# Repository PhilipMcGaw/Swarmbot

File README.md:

# SwarmBot

## Physical design constraints

* Smallest 3D Printer maximum dimensions 100 x 100 x 100
* Largest Cheap PCB from China 100 x 100 FR4 (50¢ each)

## People who have contributed

 * Philip 'Skippy' McGaw - philip@mcgaw.eu - https://philipmcgaw.com
 * Tamarisk 'NotQuiteHere' McGaw - tamarisk@mcgaw.eu - https://tamarisk.it
 * Bob 'thinkl33t' Clough - bob@clough.me - https://thinkl33t.co.uk

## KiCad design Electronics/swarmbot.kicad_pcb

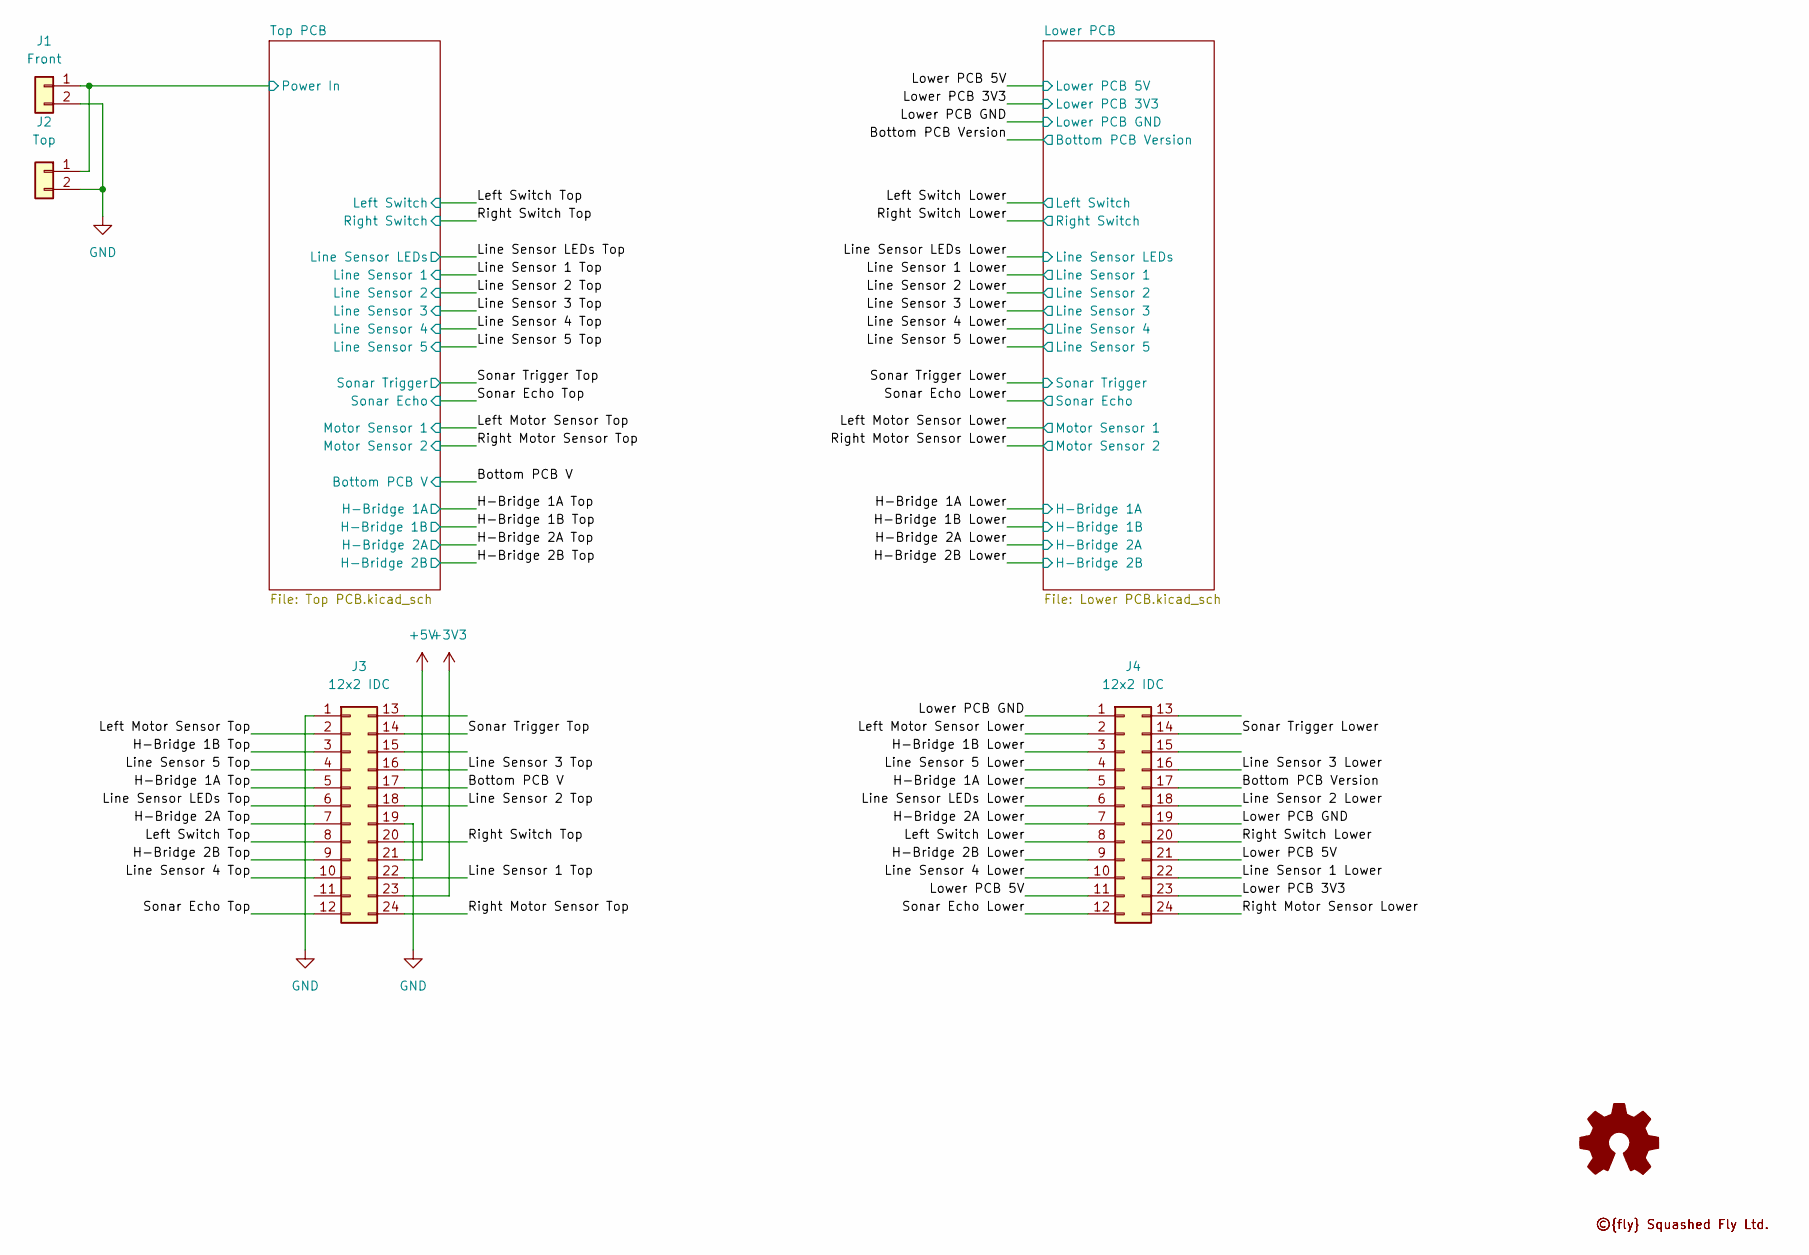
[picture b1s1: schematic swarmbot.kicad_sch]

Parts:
J1: Front; JST_XH_B2B-XH-A_1x02_P2.50mm_Vertical
J2: Top; JST_XH_B2B-XH-A_1x02_P2.50mm_Vertical
J3, J4: 12x2 IDC; IDC-Header_2x12_P2.54mm_Vertical
LOGO1: Logo_Open_Hardware_Small; OSHW-Logo2_7.3x6mm_SilkScreen
Logo1, Logo2: SquashedFlyLogo; SquashedFlySilk

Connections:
+3V3: J3.23; also elsewhere on the board
+5V: J3.21; also elsewhere on the board
/Bottom PCB V: J3.17; also elsewhere on the board
/Bottom PCB Version: J4.17; also elsewhere on the board
/H-Bridge 1A Lower: J4.5; also elsewhere on the board
/H-Bridge 1A Top: J3.5; also elsewhere on the board
/H-Bridge 1B Lower: J4.3; also elsewhere on the board
/H-Bridge 1B Top: J3.3; also elsewhere on the board
/H-Bridge 2A Lower: J4.7; also elsewhere on the board
/H-Bridge 2A Top: J3.7; also elsewhere on the board
/H-Bridge 2B Lower: J4.9; also elsewhere on the board
/H-Bridge 2B Top: J3.9; also elsewhere on the board
/Left Motor Sensor Lower: J4.2; also elsewhere on the board
/Left Motor Sensor Top: J3.2; also elsewhere on the board
/Left Switch Lower: J4.8; also elsewhere on the board
/Left Switch Top: J3.8; also elsewhere on the board
/Line Sensor 1 Lower: J4.22; also elsewhere on the board
/Line Sensor 1 Top: J3.22; also elsewhere on the board
/Line Sensor 2 Lower: J4.18; also elsewhere on the board
/Line Sensor 2 Top: J3.18; also elsewhere on the board
/Line Sensor 3 Lower: J4.16; also elsewhere on the board
/Line Sensor 3 Top: J3.16; also elsewhere on the board
/Line Sensor 4 Lower: J4.10; also elsewhere on the board
/Line Sensor 4 Top: J3.10; also elsewhere on the board
/Line Sensor 5 Lower: J4.4; also elsewhere on the board
/Line Sensor 5 Top: J3.4; also elsewhere on the board
/Line Sensor LEDs Lower: J4.6; also elsewhere on the board
/Line Sensor LEDs Top: J3.6; also elsewhere on the board
/Lower PCB 3V3: J4.23; also elsewhere on the board
/Lower PCB 5V: J4.11, J4.21; also elsewhere on the board
/Lower PCB GND: J4.1, J4.19; also elsewhere on the board
/Right Motor Sensor Lower: J4.24; also elsewhere on the board
/Right Motor Sensor Top: J3.24; also elsewhere on the board
/Right Switch Lower: J4.20; also elsewhere on the board
/Right Switch Top: J3.20; also elsewhere on the board
/Sonar Echo Lower: J4.12; also elsewhere on the board
/Sonar Echo Top: J3.12; also elsewhere on the board
/Sonar Trigger Lower: J4.14; also elsewhere on the board
/Sonar Trigger Top: J3.14; also elsewhere on the board
/Top PCB/Power/Power In: J1.1, J2.1; also elsewhere on the board
GND: J1.2, J2.2, J3.1, J3.19; also elsewhere on the board

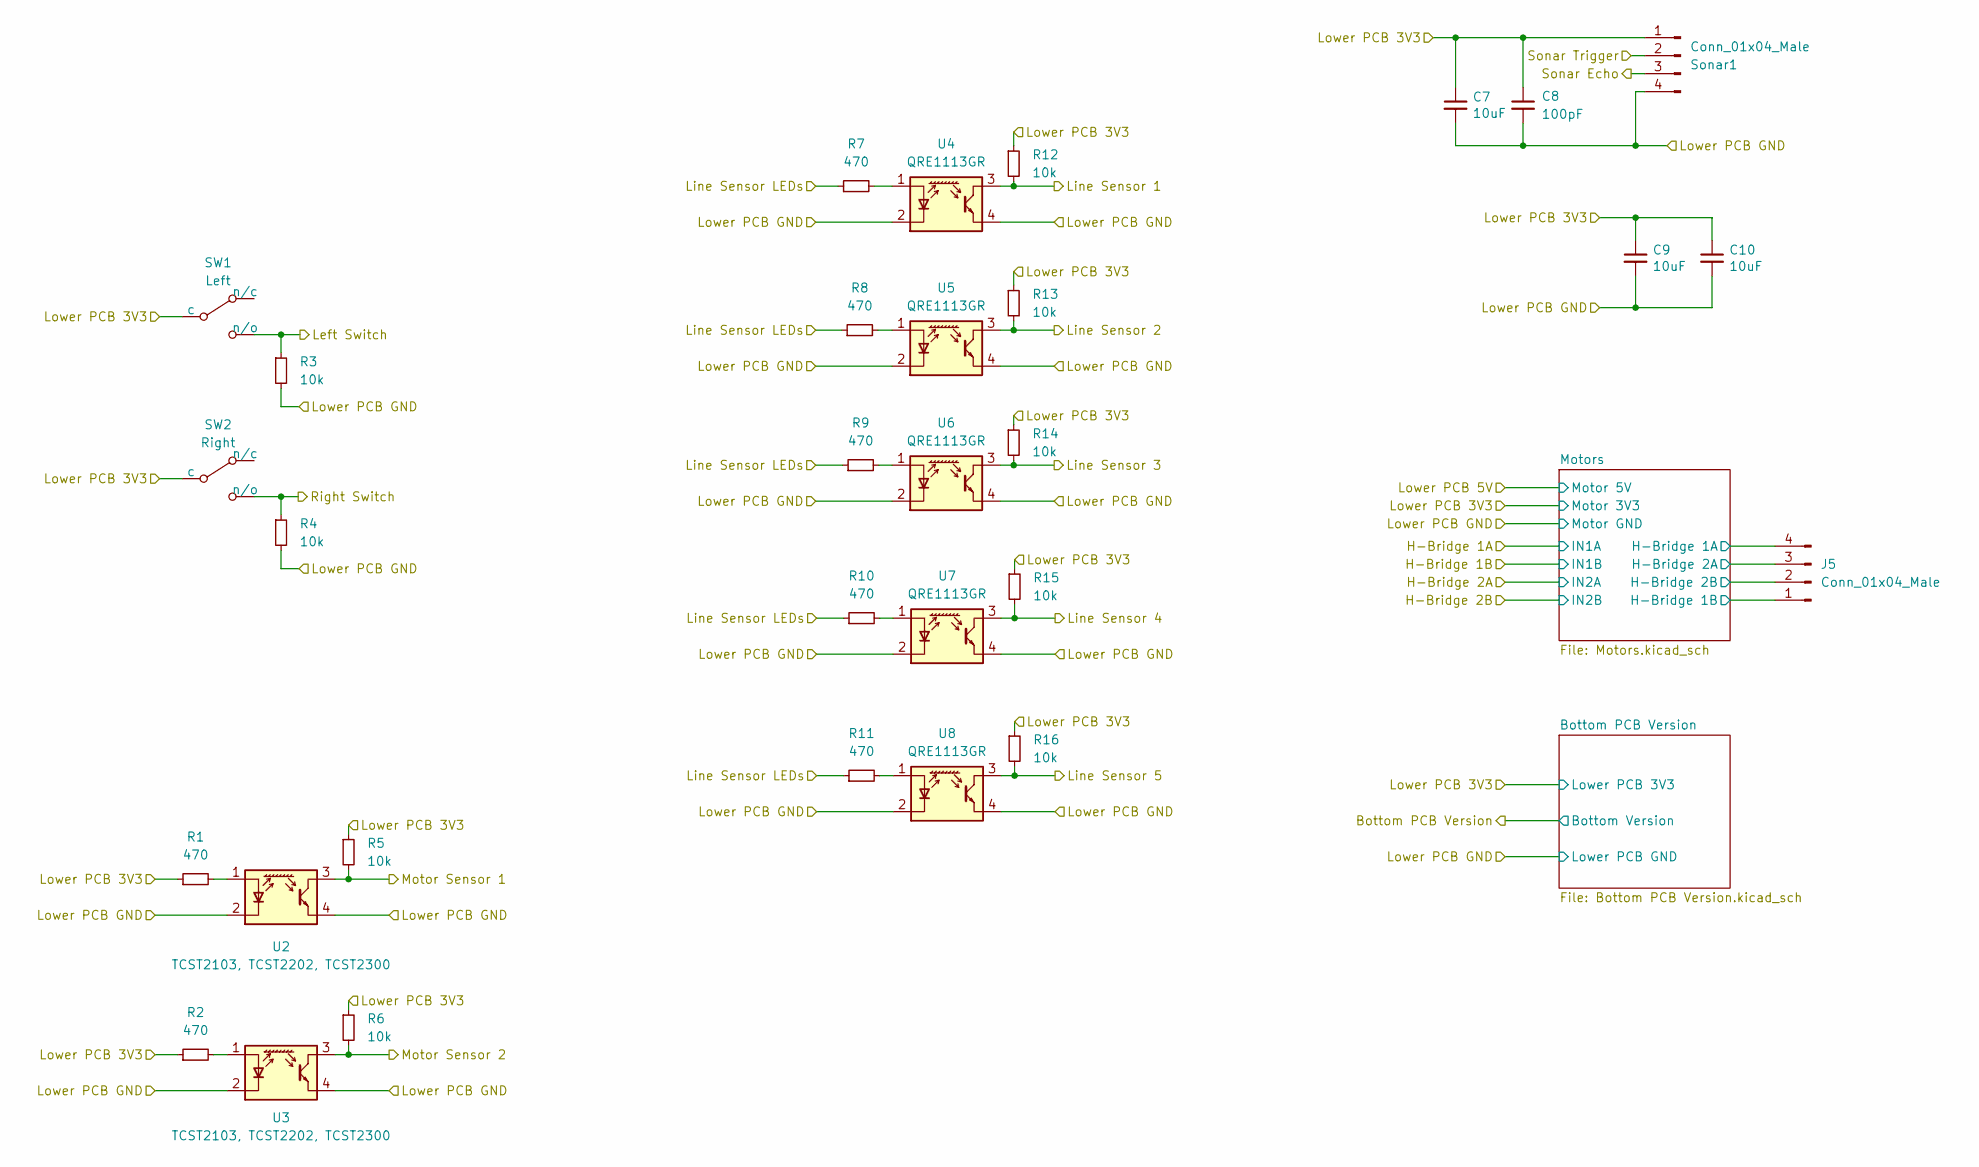
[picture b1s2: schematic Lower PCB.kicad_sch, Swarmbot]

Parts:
C7, C9, C10: 10uF; C_0805_2012Metric_Pad1.18x1.45mm_HandSolder
C8: 100pF; C_0805_2012Metric_Pad1.18x1.45mm_HandSolder
J5: Conn_01x04_Male; JST_PH_B4B-PH-K_1x04_P2.00mm_Vertical
R1, R2, R7, R8, R9, R10, R11: 470; R_0805_2012Metric_Pad1.20x1.40mm_HandSolder
R3, R4, R5, R6, R12, R13, R14, R15, R16: 10k; R_0805_2012Metric_Pad1.20x1.40mm_HandSolder
SW1: Left; TypeD
SW2: Right; TypeC
Sonar1: Conn_01x04_Male; PinSocket_1x04_P2.54mm_Vertical
U2, U3: TCST2103, TCST2202, TCST2300
U4, U5, U6, U7, U8: QRE1113GR; OnSemi_CASE100CY

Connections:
/Left Motor Sensor Lower: R5.2, U2.3; also elsewhere on the board
/Left Switch Lower: R3.1, SW1.2 (n/o); also elsewhere on the board
/Line Sensor 1 Lower: R12.2, U4.3; also elsewhere on the board
/Line Sensor 2 Lower: R13.2, U5.3; also elsewhere on the board
/Line Sensor 3 Lower: R14.2, U6.3; also elsewhere on the board
/Line Sensor 4 Lower: R15.2, U7.3; also elsewhere on the board
/Line Sensor 5 Lower: R16.2, U8.3; also elsewhere on the board
/Line Sensor LEDs Lower: R7.1, R8.1, R9.1, R10.1, R11.1; also elsewhere on the board
/Lower PCB 3V3: C7.1, C8.1, C9.1, C10.1, R1.1, R2.1, R5.1, R6.1, R12.1, R13.1, R14.1, R15.1, R16.1, SW1.1 (c), SW2.1 (c), Sonar1.1; also elsewhere on the board
/Lower PCB GND: C7.2, C8.2, C9.2, C10.2, R3.2, R4.2, Sonar1.4, U2.2 (K), U2.4, U3.2 (K), U3.4, U4.2 (K), U4.4, U5.2 (K), U5.4, U6.2 (K), U6.4, U7.2 (K), U7.4, U8.2 (K), U8.4; also elsewhere on the board
/Lower PCB/Motors/Motor 1A: J5.4; also elsewhere on the board
/Lower PCB/Motors/Motor 1B: J5.1; also elsewhere on the board
/Lower PCB/Motors/Motor 2A: J5.3; also elsewhere on the board
/Lower PCB/Motors/Motor 2B: J5.2; also elsewhere on the board
/Right Motor Sensor Lower: R6.2, U3.3; also elsewhere on the board
/Right Switch Lower: R4.1, SW2.2 (n/o); also elsewhere on the board
/Sonar Echo Lower: Sonar1.3; also elsewhere on the board
/Sonar Trigger Lower: Sonar1.2; also elsewhere on the board
unnamed: R1.2, U2.1 (A)
unnamed: R2.2, U3.1 (A)
unnamed: R7.2, U4.1 (A)
unnamed: R8.2, U5.1 (A)
unnamed: R9.2, U6.1 (A)
unnamed: R10.2, U7.1 (A)
unnamed: R11.2, U8.1 (A)

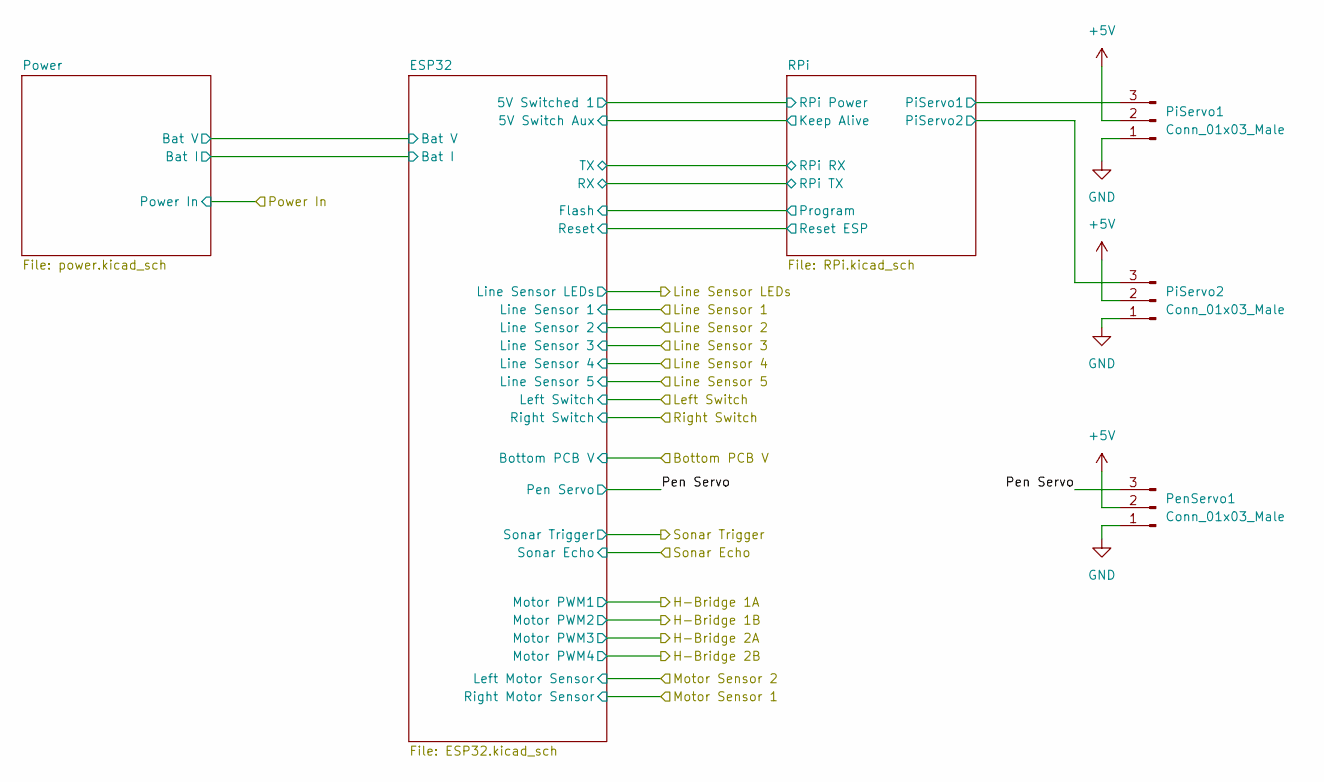
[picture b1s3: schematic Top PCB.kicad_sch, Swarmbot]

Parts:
PenServo1: Conn_01x03_Male; PinHeader_1x03_P2.54mm_Vertical
PiServo1, PiServo2: Conn_01x03_Male; PinHeader_1x03_P2.54mm_Vertical

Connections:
+5V: PenServo1.2, PiServo1.2, PiServo2.2; also elsewhere on the board
/Top PCB/Pen Servo: PenServo1.3; also elsewhere on the board
/Top PCB/RPi/PiServo1: PiServo1.3; also elsewhere on the board
/Top PCB/RPi/PiServo2: PiServo2.3; also elsewhere on the board
GND: PenServo1.1, PiServo1.1, PiServo2.1; also elsewhere on the board

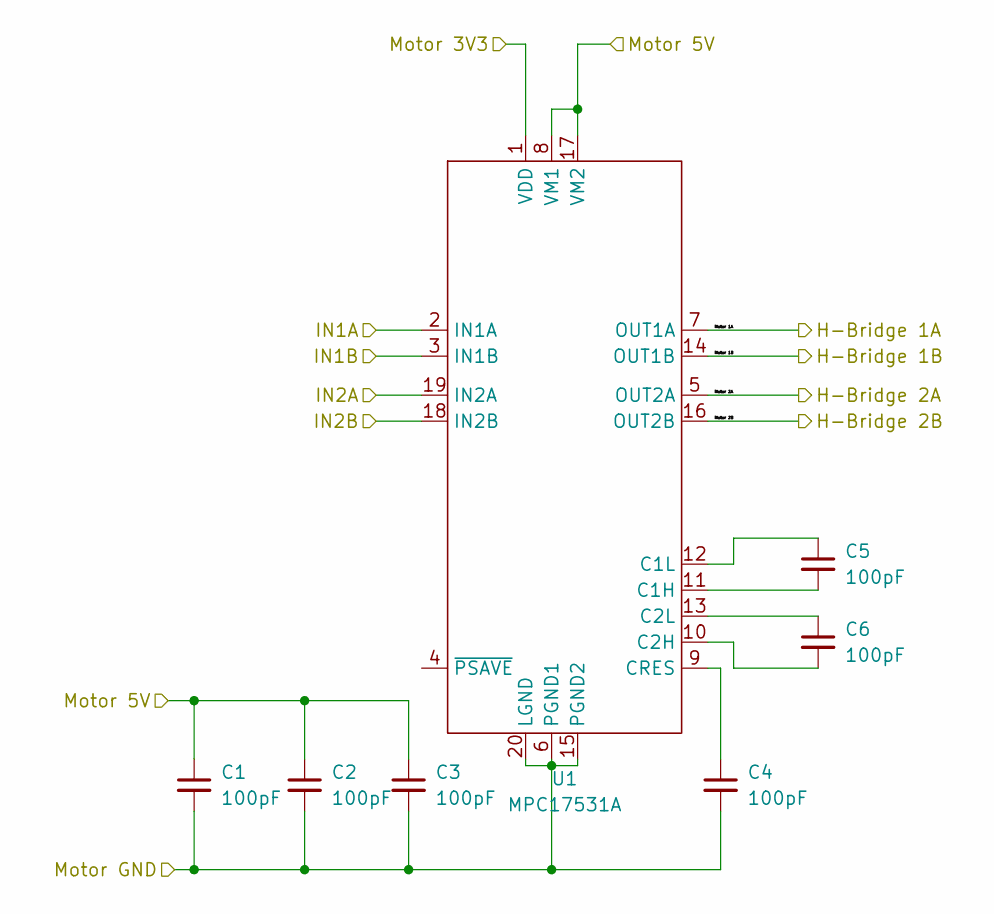
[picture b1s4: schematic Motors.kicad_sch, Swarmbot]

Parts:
C1, C2, C3, C4, C5, C6: 100pF; C_0805_2012Metric_Pad1.18x1.45mm_HandSolder
U1: MPC17531A; HTSSOP-20-1EP_4.4x6.5mm_P0.65mm_EP3.4x6.5mm_Mask2.75x3.43mm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; Farnell 2890075

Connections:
/H-Bridge 1A Lower: U1.2 (IN1A); also elsewhere on the board
/H-Bridge 1B Lower: U1.3 (IN1B); also elsewhere on the board
/H-Bridge 2A Lower: U1.19 (IN2A); also elsewhere on the board
/H-Bridge 2B Lower: U1.18 (IN2B); also elsewhere on the board
/Lower PCB 3V3: U1.1 (VDD); also elsewhere on the board
/Lower PCB 5V: C1.1, C2.1, C3.1, U1.8 (VM1), U1.17 (VM2); also elsewhere on the board
/Lower PCB GND: C1.2, C2.2, C3.2, C4.2, U1.6 (PGND1), U1.15 (PGND2), U1.20 (LGND); also elsewhere on the board
/Lower PCB/Motors/Motor 1A: U1.7 (OUT1A); also elsewhere on the board
/Lower PCB/Motors/Motor 1B: U1.14 (OUT1B); also elsewhere on the board
/Lower PCB/Motors/Motor 2A: U1.5 (OUT2A); also elsewhere on the board
/Lower PCB/Motors/Motor 2B: U1.16 (OUT2B); also elsewhere on the board
unnamed: C4.1, U1.9 (CRES)
unnamed: C5.1, U1.12 (C1L)
unnamed: C5.2, U1.11 (C1H)
unnamed: C6.1, U1.13 (C2L)
unnamed: C6.2, U1.10 (C2H)

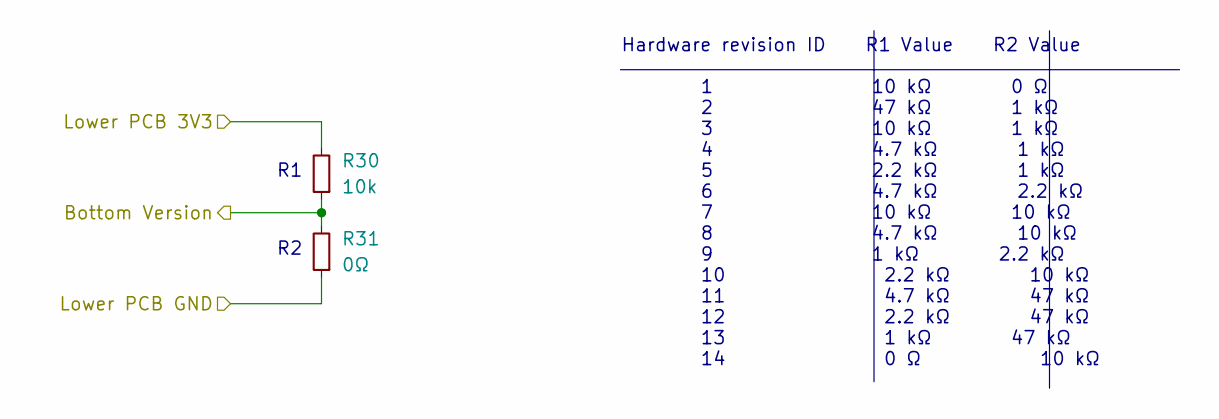
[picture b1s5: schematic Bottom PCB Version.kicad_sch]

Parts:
R30: 10k; R_0805_2012Metric_Pad1.20x1.40mm_HandSolder
R31: 0Ω; R_0805_2012Metric_Pad1.20x1.40mm_HandSolder

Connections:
/Bottom PCB Version: R30.1, R31.2; also elsewhere on the board
/Lower PCB 3V3: R30.2; also elsewhere on the board
/Lower PCB GND: R31.1; also elsewhere on the board

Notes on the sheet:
Hardware revision ID R1 Value R2 Value 1 10 kΩ 0 Ω 2 47 kΩ 1 kΩ 3 10 kΩ 1 kΩ 4 4.7 kΩ 1 kΩ 5 2.2 kΩ 1 kΩ 6 4.7 kΩ 2.2 kΩ 7 10 kΩ 10 kΩ 8 4.7 kΩ 10 kΩ 9 1 kΩ 2.2 kΩ 10 2.2 kΩ 10 kΩ 11 4.7 kΩ 47 kΩ 12 2.2 kΩ 47 kΩ 13 1 kΩ 47 kΩ 14 0 Ω 10 kΩ

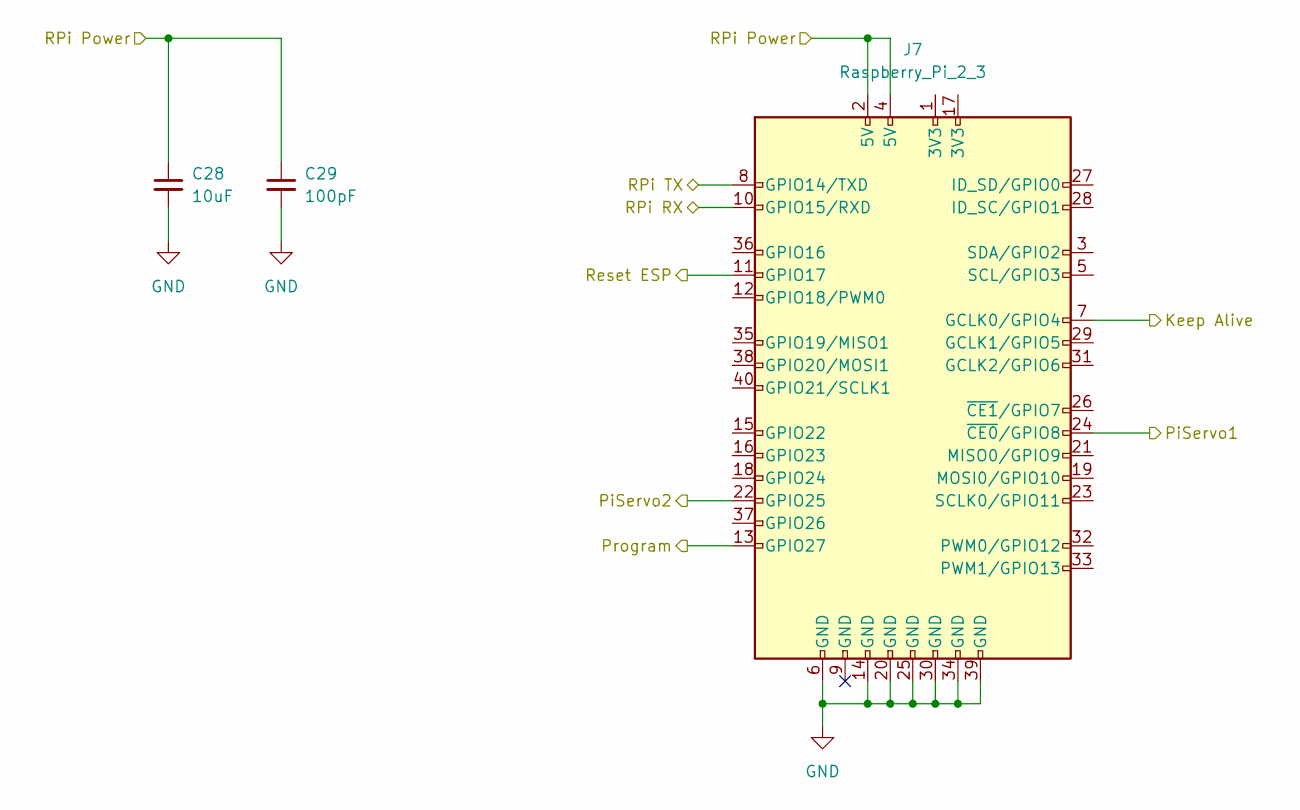
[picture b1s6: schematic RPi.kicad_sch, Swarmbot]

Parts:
C28: 10uF; C_0805_2012Metric_Pad1.18x1.45mm_HandSolder
C29: 100pF; C_0805_2012Metric_Pad1.18x1.45mm_HandSolder
J7: Raspberry_Pi_2_3; PinHeader_2x20_P2.54mm_Vertical

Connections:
/Top PCB/ESP32/5V Switch Aux: J7.7 (GCLK0/GPIO4); also elsewhere on the board
/Top PCB/ESP32/5V Switched 1: C28.1, C29.1, J7.2 (5V), J7.4 (5V); also elsewhere on the board
/Top PCB/ESP32/Flash: J7.13 (GPIO27); also elsewhere on the board
/Top PCB/ESP32/RX: J7.8 (GPIO14/TXD); also elsewhere on the board
/Top PCB/ESP32/Reset: J7.11 (GPIO17); also elsewhere on the board
/Top PCB/ESP32/TX: J7.10 (GPIO15/RXD); also elsewhere on the board
/Top PCB/RPi/PiServo1: J7.24 (~CE0/GPIO8); also elsewhere on the board
/Top PCB/RPi/PiServo2: J7.22 (GPIO25); also elsewhere on the board
GND: C28.2, C29.2, J7.6 (GND), J7.14 (GND), J7.20 (GND), J7.25 (GND), J7.30 (GND), J7.34 (GND), J7.39 (GND); also elsewhere on the board

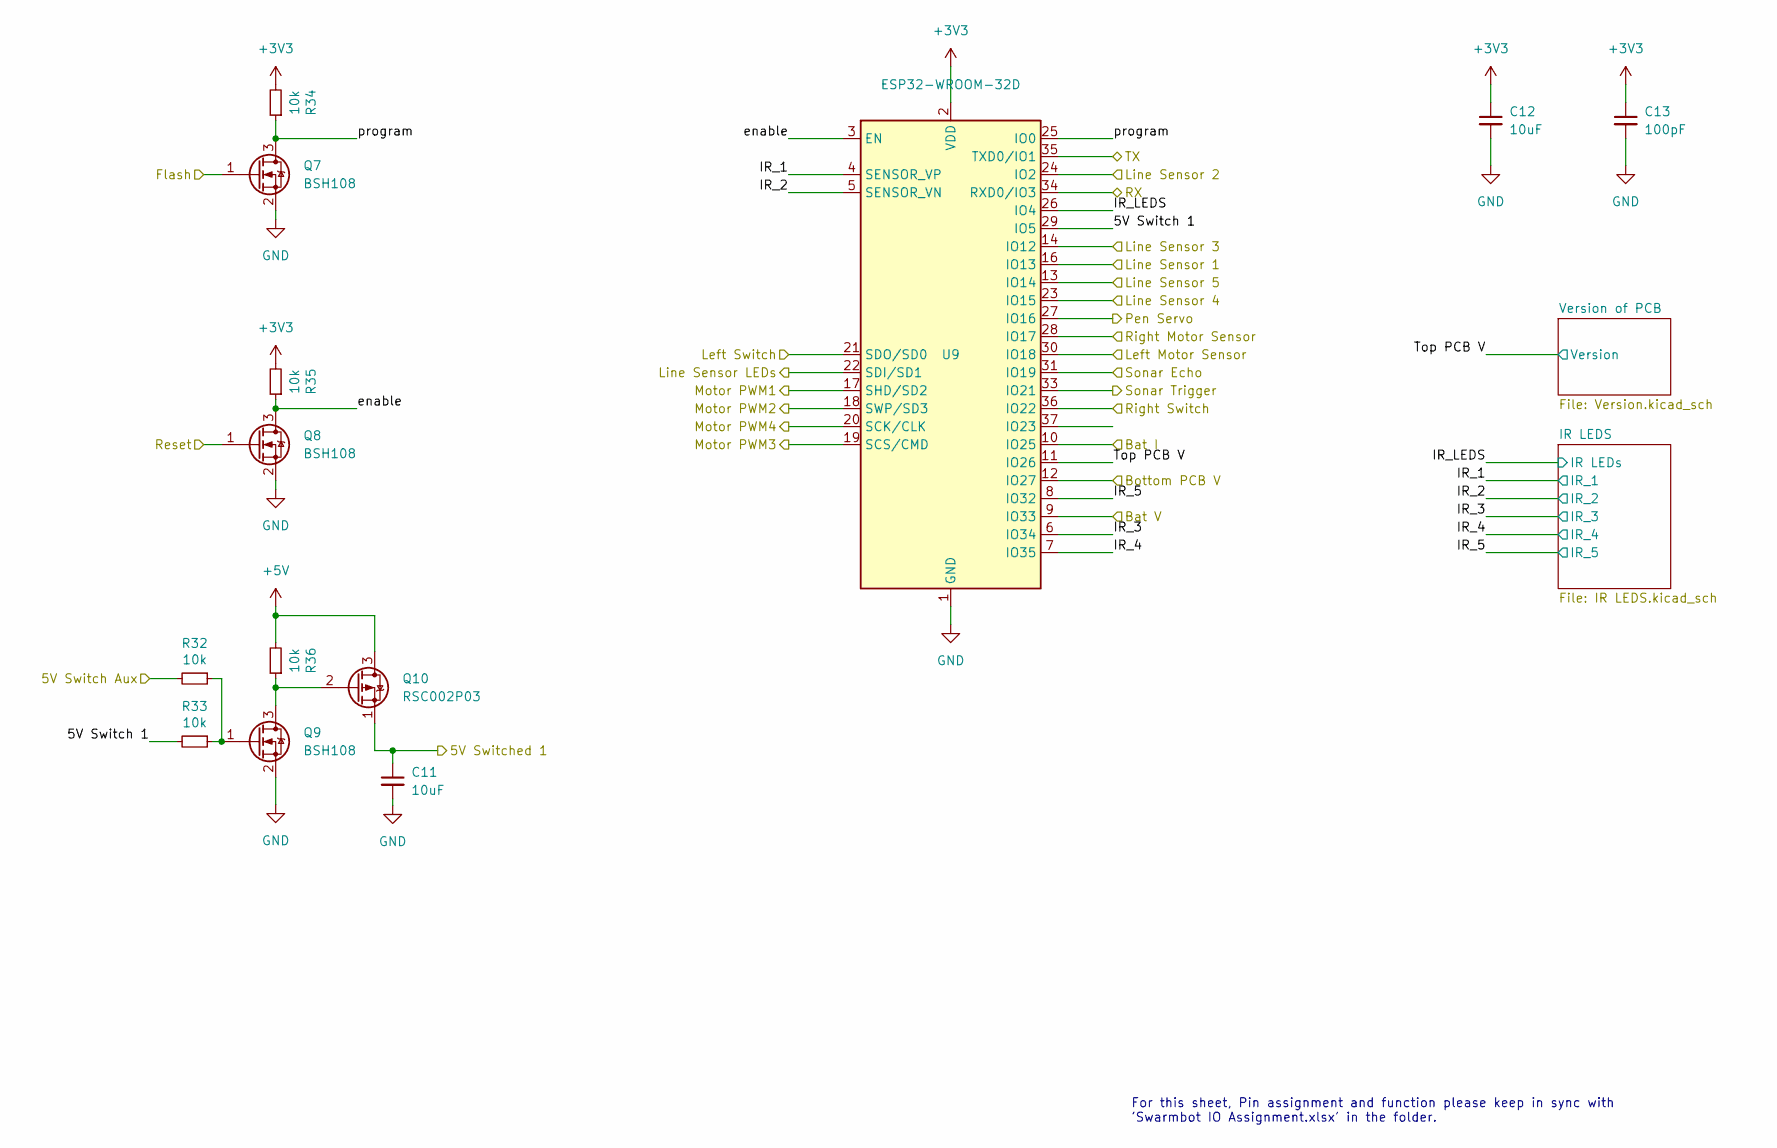
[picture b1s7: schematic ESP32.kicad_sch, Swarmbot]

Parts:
C11, C12: 10uF; C_0805_2012Metric_Pad1.18x1.45mm_HandSolder
C13: 100pF; C_0805_2012Metric_Pad1.18x1.45mm_HandSolder
Q7, Q8, Q9: BSH108; SOT-23; Farnell 1758067
Q10: RSC002P03; SOT-23; Farnell 2706652
R32, R33, R34, R35, R36: 10k; R_0805_2012Metric_Pad1.20x1.40mm_HandSolder
U9: ESP32-WROOM-32D; ESP32-WROOM-32

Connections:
+3V3: C12.1, C13.1, R34.2, R35.2, U9.2 (VDD); also elsewhere on the board
+5V: Q10.3 (D), R36.2; also elsewhere on the board
/Bottom PCB V: U9.12 (IO27); also elsewhere on the board
/H-Bridge 1A Top: U9.17 (SHD/SD2); also elsewhere on the board
/H-Bridge 1B Top: U9.18 (SWP/SD3); also elsewhere on the board
/H-Bridge 2A Top: U9.19 (SCS/CMD); also elsewhere on the board
/H-Bridge 2B Top: U9.20 (SCK/CLK); also elsewhere on the board
/Left Motor Sensor Top: U9.28 (IO17); also elsewhere on the board
/Left Switch Top: U9.21 (SDO/SD0); also elsewhere on the board
/Line Sensor 1 Top: U9.16 (IO13); also elsewhere on the board
/Line Sensor 2 Top: U9.24 (IO2); also elsewhere on the board
/Line Sensor 3 Top: U9.14 (IO12); also elsewhere on the board
/Line Sensor 4 Top: U9.23 (IO15); also elsewhere on the board
/Line Sensor 5 Top: U9.13 (IO14); also elsewhere on the board
/Line Sensor LEDs Top: U9.22 (SDI/SD1); also elsewhere on the board
/Right Motor Sensor Top: U9.30 (IO18); also elsewhere on the board
/Right Switch Top: U9.36 (IO22); also elsewhere on the board
/Sonar Echo Top: U9.31 (IO19); also elsewhere on the board
/Sonar Trigger Top: U9.33 (IO21); also elsewhere on the board
/Top PCB/ESP32/5V Switch 1: R33.2, U9.29 (IO5)
/Top PCB/ESP32/5V Switch Aux: R32.2; also elsewhere on the board
/Top PCB/ESP32/5V Switched 1: C11.1, Q10.1 (S); also elsewhere on the board
/Top PCB/ESP32/Bat I: U9.10 (IO25); also elsewhere on the board
/Top PCB/ESP32/Bat V: U9.9 (IO33); also elsewhere on the board
/Top PCB/ESP32/Flash: Q7.1 (G); also elsewhere on the board
/Top PCB/ESP32/IR_1: U9.4 (SENSOR_VP); also elsewhere on the board
/Top PCB/ESP32/IR_2: U9.5 (SENSOR_VN); also elsewhere on the board
/Top PCB/ESP32/IR_3: U9.6 (IO34); also elsewhere on the board
/Top PCB/ESP32/IR_4: U9.7 (IO35); also elsewhere on the board
/Top PCB/ESP32/IR_5: U9.8 (IO32); also elsewhere on the board
/Top PCB/ESP32/IR_LEDS: U9.26 (IO4); also elsewhere on the board
/Top PCB/ESP32/RX: U9.34 (RXD0/IO3); also elsewhere on the board
/Top PCB/ESP32/Reset: Q8.1 (G); also elsewhere on the board
/Top PCB/ESP32/TX: U9.35 (TXD0/IO1); also elsewhere on the board
/Top PCB/ESP32/Top PCB V: U9.11 (IO26); also elsewhere on the board
/Top PCB/ESP32/enable: Q8.3 (D), R35.1, U9.3 (EN)
/Top PCB/ESP32/program: Q7.3 (D), R34.1, U9.25 (IO0)
/Top PCB/Pen Servo: U9.27 (IO16); also elsewhere on the board
GND: C11.2, C12.2, C13.2, Q7.2 (S), Q8.2 (S), Q9.2 (S), U9.1 (GND), U9.15 (GND), U9.38 (GND), U9.39 (GND); also elsewhere on the board
unnamed: Q9.1 (G), R32.1, R33.1
unnamed: Q9.3 (D), Q10.2 (G), R36.1

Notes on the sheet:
For this sheet, Pin assignment and function please keep in sync with 'Swarmbot IO Assignment.xlsx' in the folder.

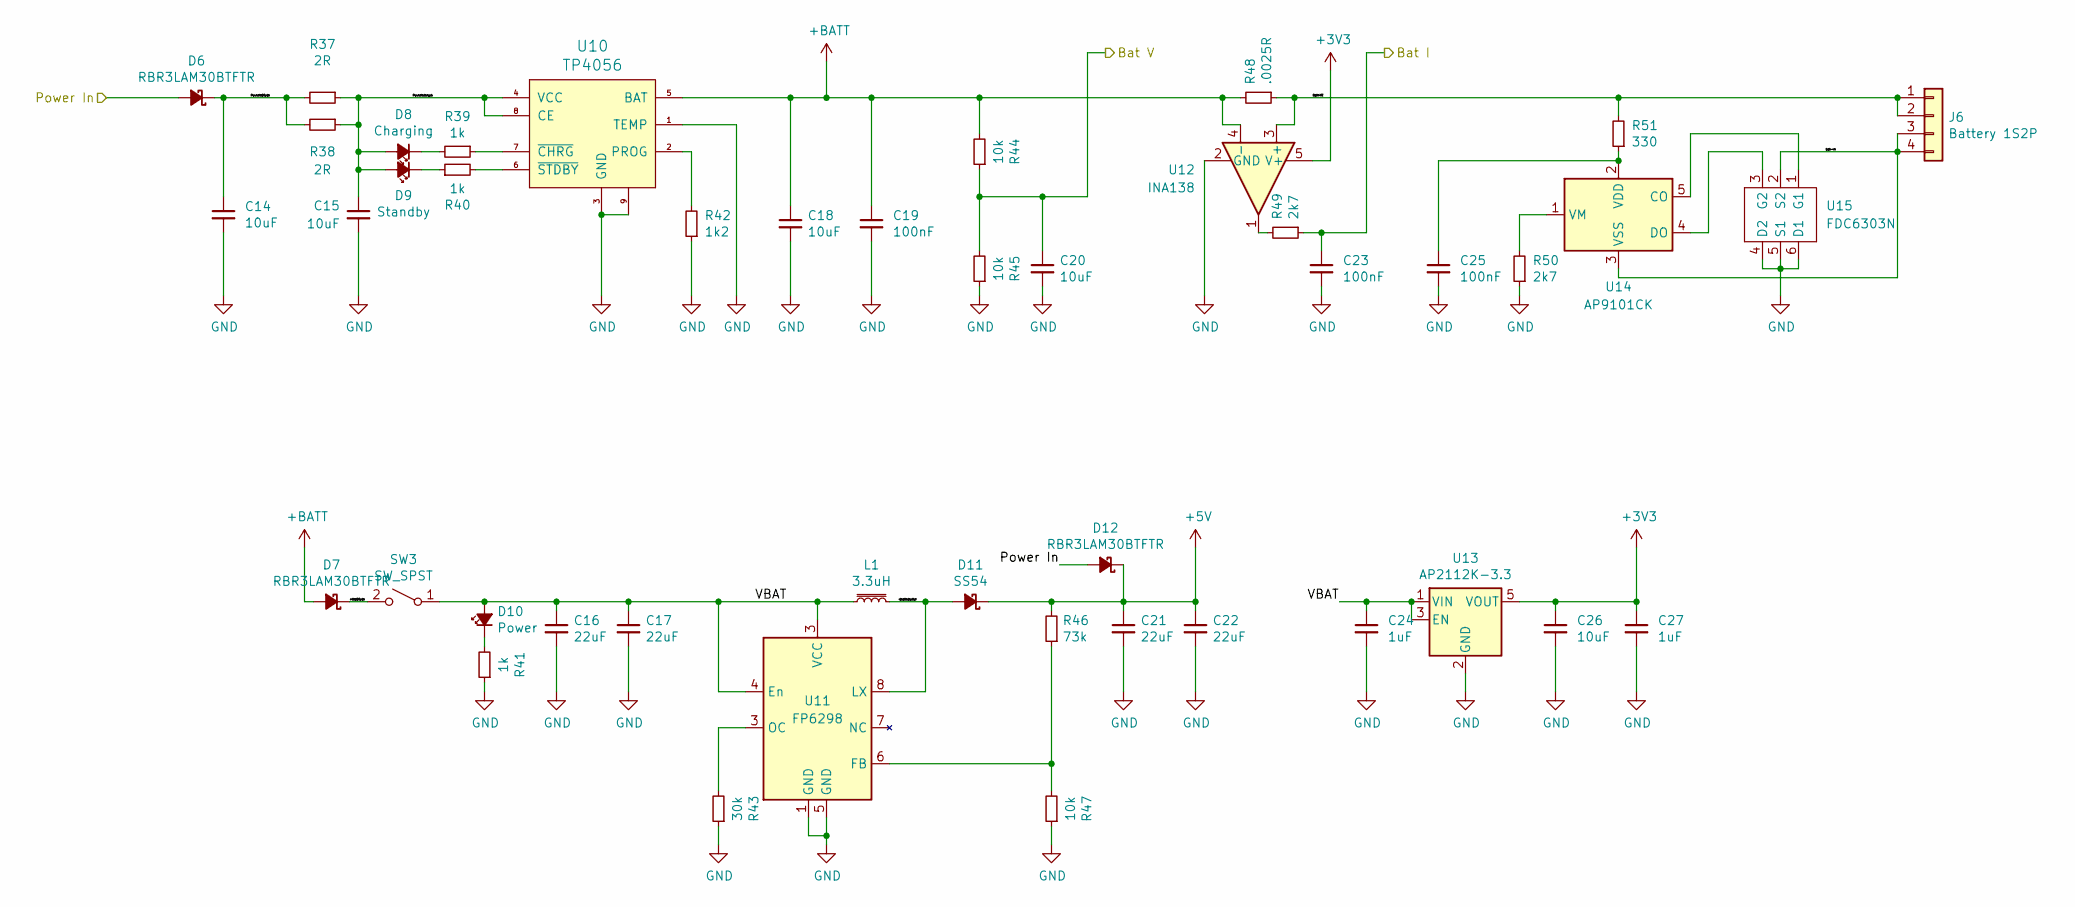
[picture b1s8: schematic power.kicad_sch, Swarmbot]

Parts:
C14, C15, C18, C20: 10uF; C_0805_2012Metric_Pad1.18x1.45mm_HandSolder
C16, C17, C21, C22: 22uF; C_0805_2012Metric_Pad1.18x1.45mm_HandSolder
C19, C23, C25: 100nF; C_0805_2012Metric_Pad1.18x1.45mm_HandSolder
C24, C27: 1uF; C_0805_2012Metric_Pad1.18x1.45mm_HandSolder; mpn MF-CAP-0603-1uF
C26: 10uF; C_0805_2012Metric_Pad1.18x1.45mm_HandSolder; mpn MF-CAP-1206-10uF
D6, D7, D12: RBR3LAM30BTFTR; D_SOD-128; Farnell 2772718
D8: Charging; LED_0805_2012Metric_Pad1.15x1.40mm_HandSolder
D9: Standby; LED_0805_2012Metric_Pad1.15x1.40mm_HandSolder
D10: Power; LED_0805_2012Metric_Pad1.15x1.40mm_HandSolder
D11: SS54; D_SMC_Handsoldering
J6: Battery 1S2P; JST_XH_B4B-XH-A_1x04_P2.50mm_Vertical
L1: 3.3uH; L_6.3x6.3_H3; Farnell 2530098
R37, R38: 2R; R_0805_2012Metric_Pad1.20x1.40mm_HandSolder
R39, R40, R41: 1k; R_0805_2012Metric_Pad1.20x1.40mm_HandSolder
R42: 1k2; R_0805_2012Metric_Pad1.20x1.40mm_HandSolder
R43: 30k; R_0805_2012Metric_Pad1.20x1.40mm_HandSolder
R44, R45, R47: 10k; R_0805_2012Metric_Pad1.20x1.40mm_HandSolder
R46: 73k; R_0805_2012Metric_Pad1.20x1.40mm_HandSolder
R48: .0025R; R_1206_3216Metric_Pad1.30x1.75mm_HandSolder
R49, R50: 2k7; R_0805_2012Metric_Pad1.20x1.40mm_HandSolder
R51: 330; R_0805_2012Metric_Pad1.20x1.40mm_HandSolder
SW3: SW_SPST; SW_SPST_B3U-3000P-B
U10: TP4056; SOP-8-1EP_4.57x4.57mm_P1.27mm_EP4.57x4.45mm_ThermalVias
U11: FP6298; LCSC# C88319
U12: INA138; SOT-23-5
U13: AP2112K-3.3; SOT-23-5; mpn AP2112K-3.3TRG1
U14: AP9101CK; SOT-23-5; Farnell 3483011
U15: FDC6303N; SOT-23-6_Handsoldering

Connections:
+3V3: C26.1, C27.1, U12.5 (V+), U13.5 (VOUT); also elsewhere on the board
+5V: C21.1, C22.1, D11.1 (K), D12.1 (K), R46.2; also elsewhere on the board
+BATT: C18.1, C19.1, D7.2 (A), R44.2, R48.2, U10.5 (BAT), U12.4 (-)
/Top PCB/ESP32/Bat I: C23.1, R49.1; also elsewhere on the board
/Top PCB/ESP32/Bat V: C20.1, R44.1, R45.2; also elsewhere on the board
/Top PCB/Power/+BatDiode: D7.1 (K), SW3.2 (B)
/Top PCB/Power/Bat+VE: J6.1, J6.2, R48.1, R51.2, U12.3 (+)
/Top PCB/Power/Power In: D6.2 (A), D12.2 (A); also elsewhere on the board
/Top PCB/Power/PowerInDiode: C14.1, D6.1 (K), R37.2, R38.2
/Top PCB/Power/PowerInInrush: C15.1, D8.2 (A), D9.2 (A), R37.1, R38.1, U10.4 (VCC), U10.8 (CE)
/Top PCB/Power/VBAT: C16.1, C17.1, C24.1, D10.2 (A), L1.1, SW3.1 (A), U11.3 (OC), U11.4 (En), U13.1 (VIN), U13.3 (EN)
/Top PCB/Power/bat-ve: J6.3, J6.4, U14.3 (VSS), U15.2 (S2)
/Top PCB/Power/vbatInductor: D11.2 (A), L1.2, U11.8 (LX)
GND: C14.2, C15.2, C16.2, C17.2, C18.2, C19.2, C20.2, C21.2, C22.2, C23.2, C24.2, C25.2, C26.2, C27.2, R41.1, R42.1, R43.1, R45.1, R47.1, R50.1, U10.1 (TEMP), U10.3 (GND), U10.9, U11.1 (GND), U11.5 (GND), U12.2 (GND), U13.2 (GND), U15.4 (D2), U15.5 (S1), U15.6 (D1); also elsewhere on the board
unnamed: C25.1, R51.1, U14.2 (VDD)
unnamed: D8.1 (K), R39.2
unnamed: D9.1 (K), R40.1
unnamed: D10.1 (K), R41.2
unnamed: R39.1, U10.7 (~CHRG)
unnamed: R40.2, U10.6 (~STDBY)
unnamed: R42.2, U10.2 (PROG)
unnamed: R43.2, U11.3 (OC)
unnamed: R46.1, R47.2, U11.6 (FB)
unnamed: R49.2, U12.1
unnamed: R50.2, U14.1 (VM)
unnamed: U14.4 (DO), U15.3 (G2)
unnamed: U14.5 (CO), U15.1 (G1)

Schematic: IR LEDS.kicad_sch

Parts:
D1, D2, D3, D4, D5: IR; LED_D5.0mm
Q1: AO3400A; SOT-23
Q2, Q3, Q4, Q5, Q6: Q_Photo_NPN_CE; LED_D3.0mm_IRBlack
R19, R20, R21, R22, R23: 470; R_0805_2012Metric_Pad1.20x1.40mm_HandSolder
R24, R25, R26, R27, R28, R29: 10k; R_0805_2012Metric_Pad1.20x1.40mm_HandSolder

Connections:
+3V3: Q2.1 (C), Q3.1 (C), Q4.1 (C), Q5.1 (C), Q6.1 (C), R19.1, R20.1, R21.1, R22.1, R23.1; also elsewhere on the board
/Top PCB/ESP32/IR_1: Q2.2 (E), R25.2; also elsewhere on the board
/Top PCB/ESP32/IR_2: Q3.2 (E), R26.2; also elsewhere on the board
/Top PCB/ESP32/IR_3: Q4.2 (E), R27.2; also elsewhere on the board
/Top PCB/ESP32/IR_4: Q5.2 (E), R28.2; also elsewhere on the board
/Top PCB/ESP32/IR_5: Q6.2 (E), R29.2; also elsewhere on the board
/Top PCB/ESP32/IR_LEDS: R24.1; also elsewhere on the board
GND: Q1.2 (S), R25.1, R26.1, R27.1, R28.1, R29.1; also elsewhere on the board
unnamed: D1.1 (K), D2.1 (K), D3.1 (K), D4.1 (K), D5.1 (K), Q1.3 (D)
unnamed: D1.2 (A), R19.2
unnamed: D2.2 (A), R20.2
unnamed: D3.2 (A), R21.2
unnamed: D4.2 (A), R22.2
unnamed: D5.2 (A), R23.2
unnamed: Q1.1 (G), R24.2

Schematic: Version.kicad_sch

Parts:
R17: 10k; R_0805_2012Metric_Pad1.20x1.40mm_HandSolder
R18: 0Ω; R_0805_2012Metric_Pad1.20x1.40mm_HandSolder

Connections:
+3V3: R17.2; also elsewhere on the board
/Top PCB/ESP32/Top PCB V: R17.1, R18.2; also elsewhere on the board
GND: R18.1; also elsewhere on the board

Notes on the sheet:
Hardware revision ID R1 Value R2 Value 1 10 kΩ 0 Ω 2 47 kΩ 1 kΩ 3 10 kΩ 1 kΩ 4 4.7 kΩ 1 kΩ 5 2.2 kΩ 1 kΩ 6 4.7 kΩ 2.2 kΩ 7 10 kΩ 10 kΩ 8 4.7 kΩ 10 kΩ 9 1 kΩ 2.2 kΩ 10 2.2 kΩ 10 kΩ 11 4.7 kΩ 47 kΩ 12 2.2 kΩ 47 kΩ 13 1 kΩ 47 kΩ 14 0 Ω 10 kΩ

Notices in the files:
Electrical/Bottom PCB/Bottom PCB.kicad_pcb:
copyright Philip McGaw 2021
Electrical/Swarmbot/swarmbot.kicad_sch:
©{fly} Squashed Fly Ltd.
